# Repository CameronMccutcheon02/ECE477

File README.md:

# ECE477
Final Project Repository for ECE477 building an air hockey robot. 
Link to website repo: https://github.com/CameronMccutcheon02/ECE477Website

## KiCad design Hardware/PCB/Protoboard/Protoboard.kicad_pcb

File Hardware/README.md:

# ECE477
Hardware section of the ECE477 repository. This directory to contain all of the system diagrams, PCB files, etc relating to hardware of the robot

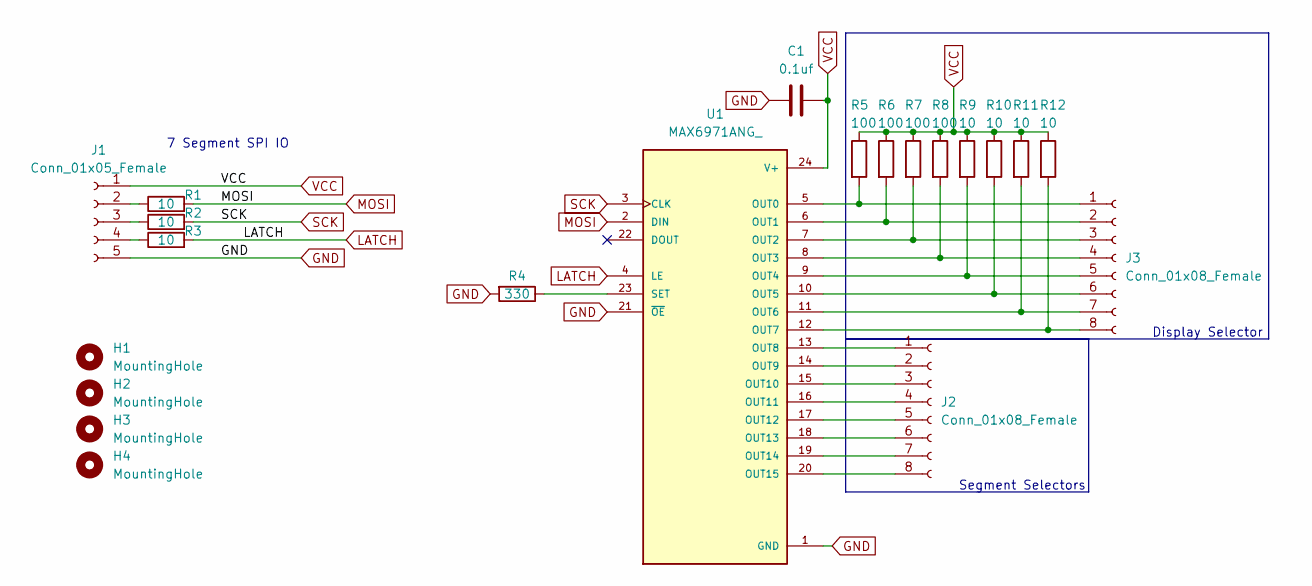
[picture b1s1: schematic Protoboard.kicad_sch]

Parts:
C1: 0.1uf; C_0805_2012Metric_Pad1.18x1.45mm_HandSolder
H1, H2, H3, H4: MountingHole; MountingHole_2.2mm_M2
J1: Conn_01x05_Female; PinSocket_1x05_P2.54mm_Vertical
J2, J3: Conn_01x08_Female; PinSocket_1x08_P2.54mm_Vertical
R1, R2, R3, R9, R10, R11, R12: 10; R_0805_2012Metric_Pad1.20x1.40mm_HandSolder
R4: 330; R_0805_2012Metric_Pad1.20x1.40mm_HandSolder
R5, R6, R7, R8: 100; R_0805_2012Metric_Pad1.20x1.40mm_HandSolder
U1: MAX6971ANG_; DIP794W47P254L3213H457Q24; PARTREV D

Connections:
GND: C1.1, J1.5, R4.2, U1.1 (GND), U1.21 (~OE)
LATCH: R3.2, U1.4 (LE)
MOSI: R1.2, U1.2 (DIN)
unnamed: J1.2, R1.1
unnamed: J1.3, R2.1
unnamed: J1.4, R3.1
unnamed: J2.1, U1.13 (OUT8)
unnamed: J2.2, U1.14 (OUT9)
unnamed: J2.3, U1.15 (OUT10)
unnamed: J2.4, U1.16 (OUT11)
unnamed: J2.5, U1.17 (OUT12)
unnamed: J2.6, U1.18 (OUT13)
unnamed: J2.7, U1.19 (OUT14)
unnamed: J2.8, U1.20 (OUT15)
unnamed: J3.1, R5.2, U1.5 (OUT0)
unnamed: J3.2, R6.2, U1.6 (OUT1)
unnamed: J3.3, R7.2, U1.7 (OUT2)
unnamed: J3.4, R8.2, U1.8 (OUT3)
unnamed: J3.5, R9.2, U1.9 (OUT4)
unnamed: J3.6, R10.2, U1.10 (OUT5)
unnamed: J3.7, R11.2, U1.11 (OUT6)
unnamed: J3.8, R12.2, U1.12 (OUT7)
unnamed: R4.1, U1.23 (SET)
SCK: R2.2, U1.3 (CLK)
VCC: C1.2, J1.1, R5.1, R6.1, R7.1, R8.1, R9.1, R10.1, R11.1, R12.1, U1.24 (V+)

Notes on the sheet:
Segment Selectors
7 Segment SPI IO
Display Selector

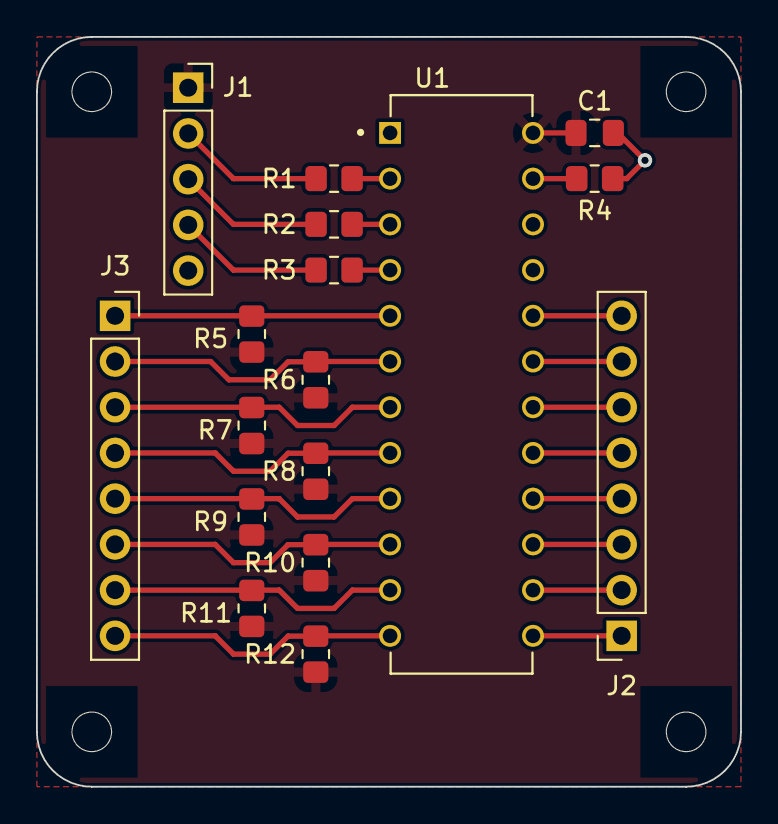
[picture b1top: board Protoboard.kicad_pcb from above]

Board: 2 copper layers, 39.1 x 41.7 mm, 21 parts (0 on the bottom side), 25 nets.

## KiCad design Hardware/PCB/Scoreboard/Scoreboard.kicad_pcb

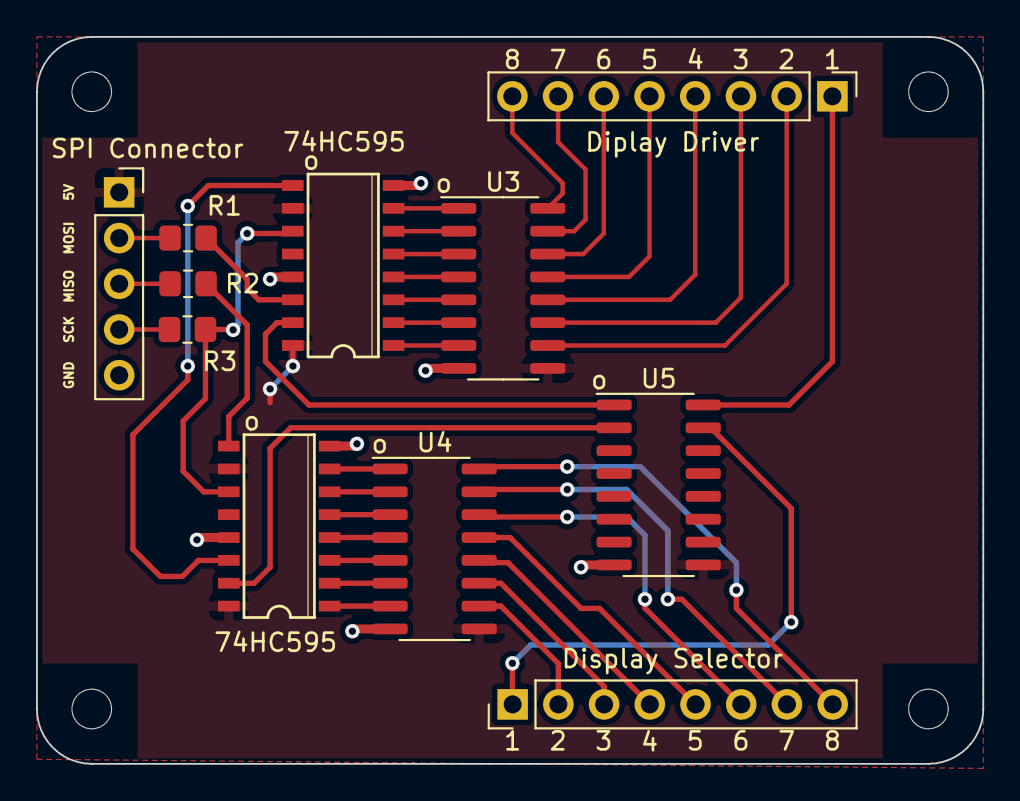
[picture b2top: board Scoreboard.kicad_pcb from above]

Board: 2 copper layers, 52.6 x 40.4 mm, 15 parts (0 on the bottom side), 41 nets.

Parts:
74HC595, 74HC595#2: 74HC595; SO16
Display Selector: Conn_01x08_Male; PinHeader_1x08_P2.54mm_Vertical
H1, H2, H3, H4: MountingHole; MountingHole_2.2mm_M2
J2: Conn_01x08_Male; PinHeader_1x08_P2.54mm_Vertical
R1, R2, R3: 10; R_0805_2012Metric_Pad1.20x1.40mm_HandSolder
SPI Connector: Conn_01x05_Female; PinSocket_1x05_P2.54mm_Vertical
U3, U4, U5: MC1413D; SOIC-16_3.9x9.9mm_P1.27mm

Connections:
/QA1: 74HC595.15 (QA), U5.1 (I1)
/QA2: 74HC595#2.15 (QA), U5.2 (I2)
/QB1: 74HC595.1 (QB), U3.7 (I7)
/QB2: 74HC595#2.1 (QB), U4.7 (I7)
/QC1: 74HC595.2 (QC), U3.6 (I6)
/QC2: 74HC595#2.2 (QC), U4.6 (I6)
/QD1: 74HC595.3 (QD), U3.5 (I5)
/QD2: 74HC595#2.3 (QD), U4.5 (I5)
/QE1: 74HC595.4 (QE), U3.4 (I4)
/QE2: 74HC595#2.4 (QE), U4.4 (I4)
/QF1: 74HC595.5 (QF), U3.3 (I3)
/QF2: 74HC595#2.5 (QF), U4.3 (I3)
/QG1: 74HC595.6 (QG), U3.2 (I2)
/QG2: 74HC595#2.6 (QG), U4.2 (I2)
/QH1: 74HC595.7 (QH), U3.1 (I1)
/QH2: 74HC595#2.7 (QH), U4.1 (I1)
/SPI1_MISO: 74HC595#2.9 (QH'), R2.2
/SPI1_MOSI: 74HC595.14 (SER), R1.2
/SPI1_SCK: 74HC595.11 (SRCLK), 74HC595#2.11 (SRCLK), R3.2
GND: 74HC595.8 (GND), 74HC595.13 (~OE), 74HC595#2.8 (GND), 74HC595#2.13 (~OE), SPI Connector.5, U3.8 (GND), U4.8 (GND), U5.8 (GND)
unnamed: R1.1, SPI Connector.2
unnamed: R2.1, SPI Connector.3
unnamed: R3.1, SPI Connector.4
unnamed: 74HC595.9 (QH'), 74HC595#2.14 (SER)
unnamed: J2.2, U3.10 (O7)
unnamed: J2.3, U3.11 (O6)
unnamed: J2.4, U3.12 (O5)
unnamed: J2.5, U3.13 (O4)
unnamed: J2.6, U3.14 (O3)
unnamed: J2.7, U3.15 (O2)
unnamed: J2.8, U3.16 (O1)
unnamed: Display Selector.2, U4.10 (O7)
unnamed: Display Selector.3, U4.11 (O6)
unnamed: Display Selector.4, U4.12 (O5)
unnamed: Display Selector.5, U4.13 (O4)
unnamed: Display Selector.6, U4.14 (O3)
unnamed: Display Selector.7, U4.15 (O2)
unnamed: Display Selector.8, U4.16 (O1)
unnamed: Display Selector.1, U5.15 (O2)
unnamed: J2.1, U5.16 (O1)
VCC: 74HC595.10 (~SRCLR), 74HC595.16 (VCC), 74HC595#2.10 (~SRCLR), 74HC595#2.16 (VCC), SPI Connector.1, U3.9 (COM), U4.9 (COM), U5.9 (COM)

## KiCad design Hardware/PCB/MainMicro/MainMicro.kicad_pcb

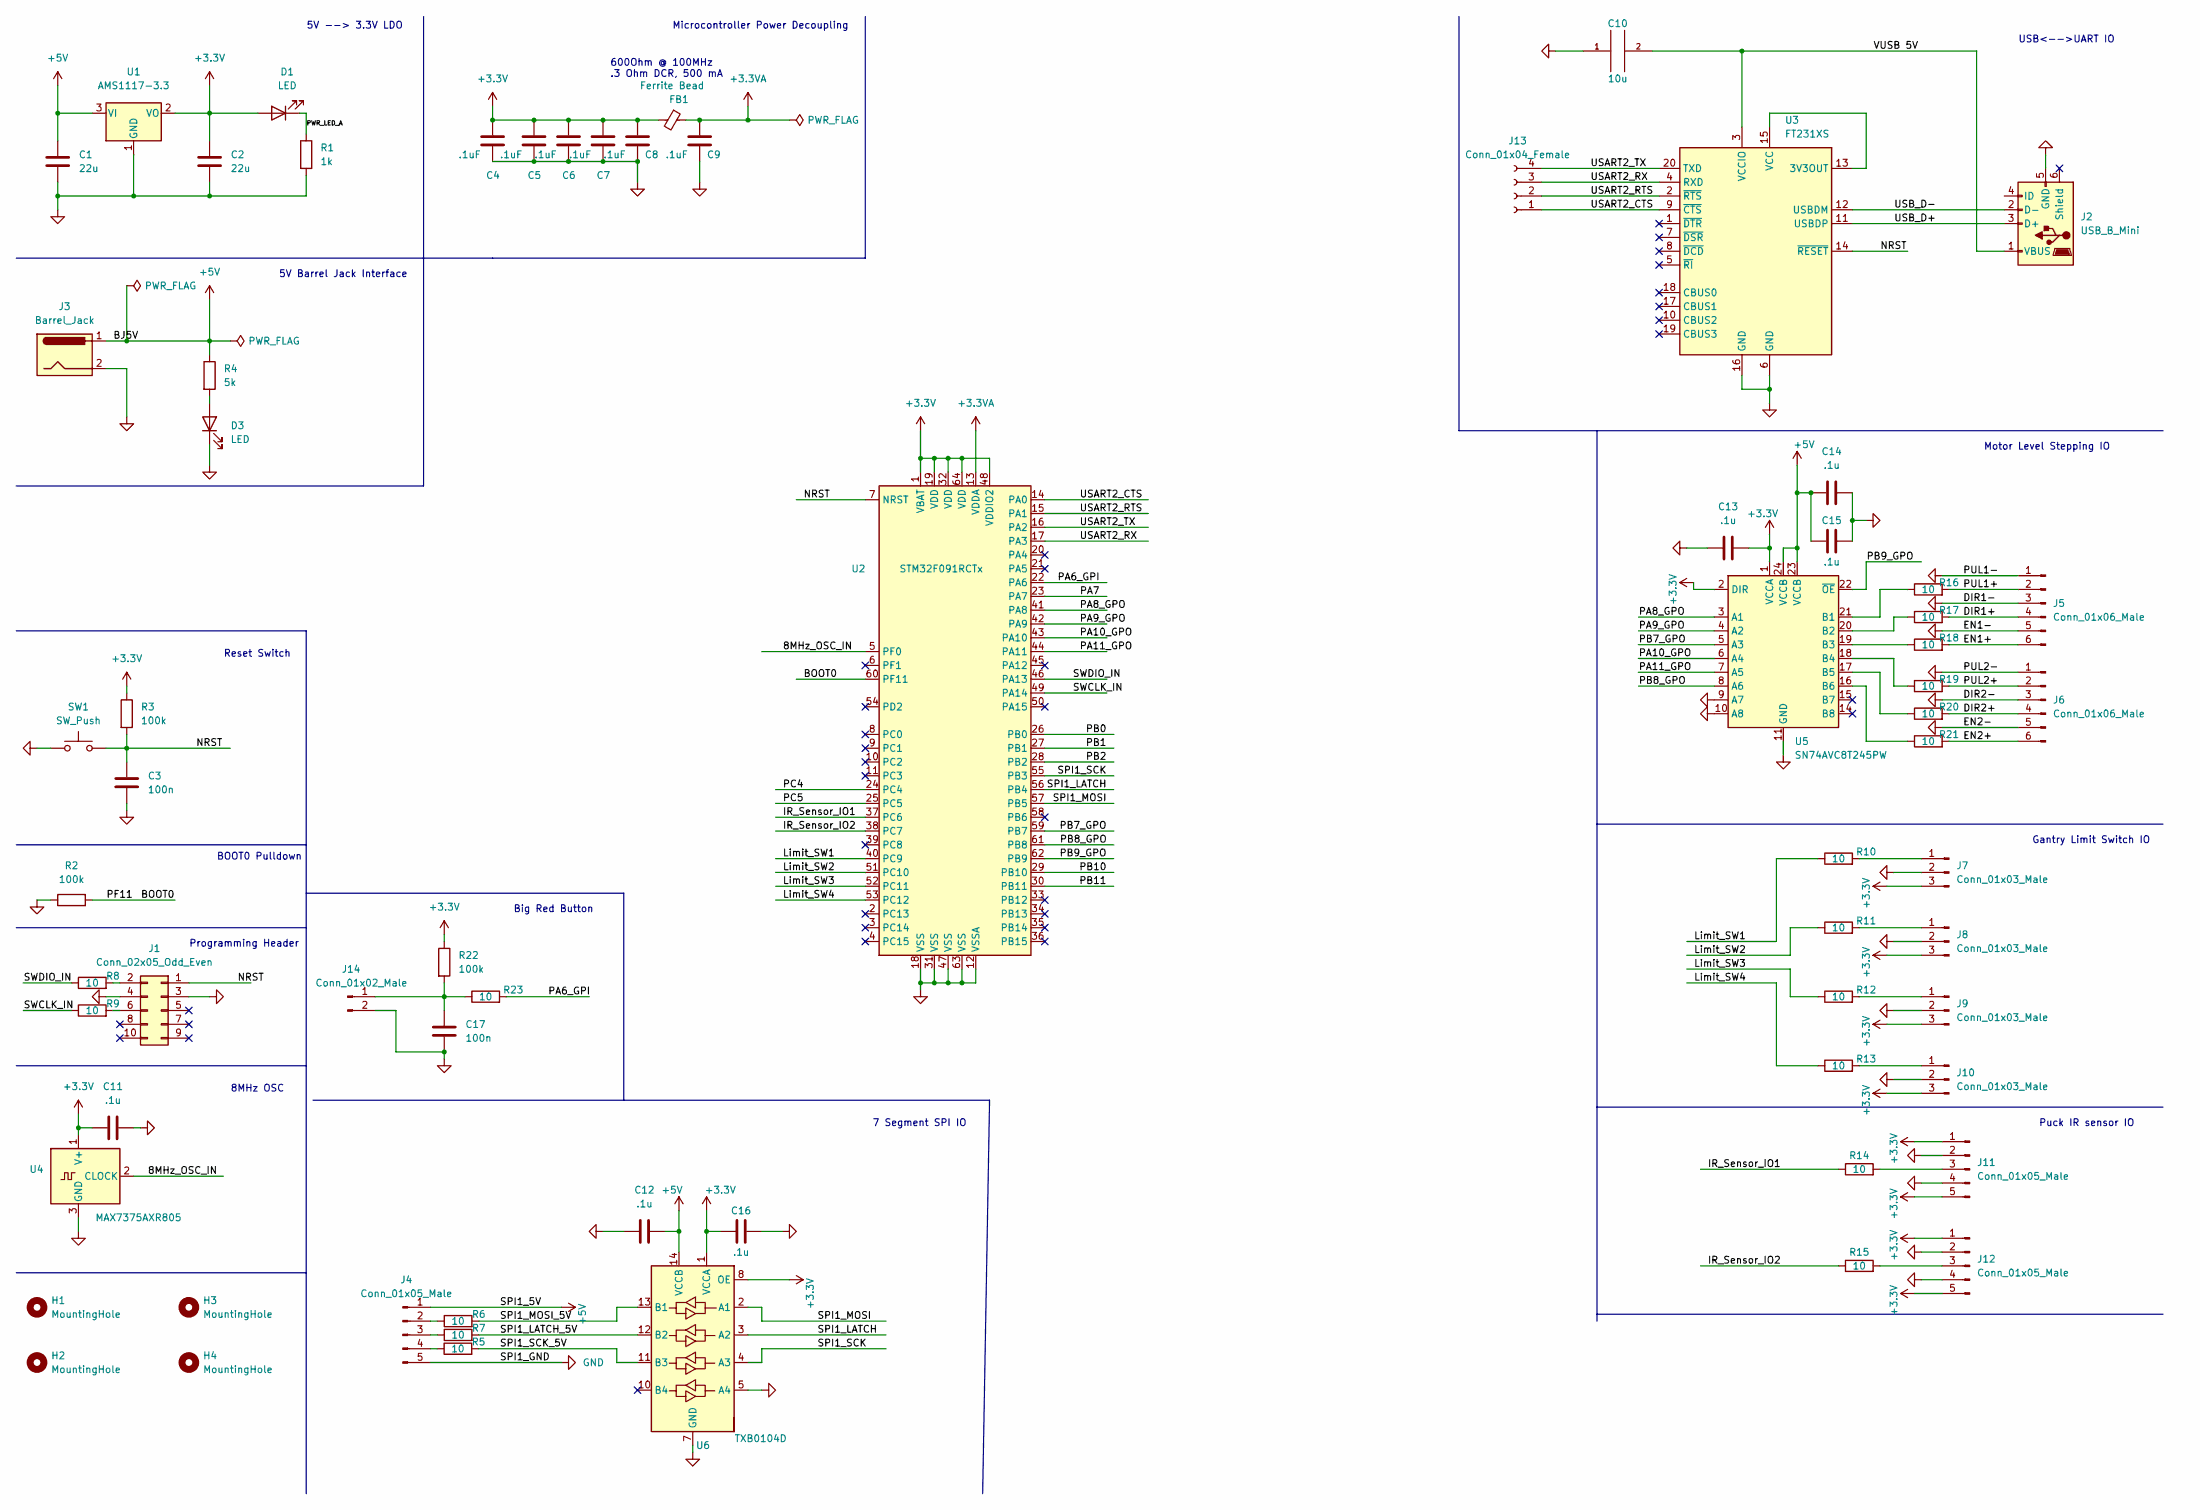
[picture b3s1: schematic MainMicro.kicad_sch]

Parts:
C1, C2: 22u; C_0805_2012Metric_Pad1.18x1.45mm_HandSolder
C3, C17: 100n; C_0805_2012Metric_Pad1.18x1.45mm_HandSolder
C4, C5, C6, C7, C8, C9: .1uF; C_0805_2012Metric_Pad1.18x1.45mm_HandSolder
C10: 10u; C_0805_2012Metric_Pad1.18x1.45mm_HandSolder
C11, C12, C13, C14, C15, C16: .1u; C_0805_2012Metric_Pad1.18x1.45mm_HandSolder
D1: LED; LED_0603_1608Metric_Pad1.05x0.95mm_HandSolder
D3: LED; LED_0805_2012Metric_Pad1.15x1.40mm_HandSolder
FB1: Ferrite Bead; L_0805_2012Metric_Pad1.15x1.40mm_HandSolder
H1, H2, H3, H4: MountingHole; MountingHole_2.7mm_M2.5
J1: Conn_02x05_Odd_Even; IDC-Header_2x05_P2.54mm_Latch_Vertical
J2: USB_B_Mini; USB_Micro-B_Amphenol_10118194_Horizontal
J3: Barrel_Jack; BarrelJack_CUI_PJ-102AH_Horizontal
J4, J11, J12: Conn_01x05_Male; JST_EH_B5B-EH-A_1x05_P2.50mm_Vertical
J5, J6: Conn_01x06_Male; JST_EH_B6B-EH-A_1x06_P2.50mm_Vertical
J7, J8, J9, J10: Conn_01x03_Male; JST_EH_B3B-EH-A_1x03_P2.50mm_Vertical
J13: Conn_01x04_Female; JST_EH_B4B-EH-A_1x04_P2.50mm_Vertical
J14: Conn_01x02_Male; JST_EH_B2B-EH-A_1x02_P2.50mm_Vertical
R1: 1k; R_0805_2012Metric_Pad1.20x1.40mm_HandSolder
R2, R3, R22: 100k; R_0805_2012Metric_Pad1.20x1.40mm_HandSolder
R4: 5k; R_0805_2012Metric_Pad1.20x1.40mm_HandSolder
R5, R6, R7, R8, R9, R10, R11, R12, R13, R14, R15, R16, R17, R18, R19, R20, R21, R23: 10; R_0805_2012Metric_Pad1.20x1.40mm_HandSolder
SW1: SW_Push; SW_SPST_PTS645
U1: AMS1117-3.3; SOT-223-3_TabPin2
U2: STM32F091RCTx; LQFP-64_10x10mm_P0.5mm
U3: FT231XS; SSOP-20_3.9x8.7mm_P0.635mm
U4: MAX7375AXR805; SOT-323_SC-70
U5: SN74AVC8T245PW; TSSOP-24_4.4x7.8mm_P0.65mm
U6: TXB0104D; SOIC-14_3.9x8.7mm_P1.27mm

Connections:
+3.3VA: C9.1, FB1.1, U2.13 (VDDA)
+3V3: C2.1, C4.1, C5.1, C6.1, C7.1, C8.1, C11.1, C13.1, C16.2, D1.2 (A), FB1.2, J7.3, J8.3, J9.3, J10.3, J11.1, J11.5, J12.1, J12.5, R3.1, R22.1, U1.2 (VO), U2.1 (VBAT), U2.19 (VDD), U2.32 (VDD), U2.48 (VDDIO2), U2.64 (VDD), U4.1 (V+), U5.1 (VCCA), U5.2 (DIR), U6.1 (VCCA), U6.8 (OE)
+5V: C1.1, C12.1, C14.2, C15.2, J3.1, J4.1, R4.1, U1.3 (VI), U5.23 (VCCB), U5.24 (VCCB), U6.14 (VCCB)
/8MHz_OSC_IN: U2.5 (PF0), U4.2 (CLOCK)
/BOOT0: R2.2, U2.60 (PF11)
/DIR1+: J5.4, R17.2
/DIR2+: J6.4, R20.2
/EN1+: J5.6, R18.2
/EN2+: J6.6, R21.2
/IR_Sensor_IO1: R14.1, U2.37 (PC6)
/IR_Sensor_IO2: R15.1, U2.38 (PC7)
/Limit_SW1: R10.1, U2.40 (PC9)
/Limit_SW2: R11.1, U2.51 (PC10)
/Limit_SW3: R12.1, U2.52 (PC11)
/Limit_SW4: R13.1, U2.53 (PC12)
/NRST: C3.1, J1.1, R3.2, SW1.2, U2.7 (NRST), U3.14 (~RESET)
/PA6_GPI: R23.2, U2.22 (PA6)
/PA7: U2.23 (PA7)
/PA8_GPO: U2.41 (PA8), U5.3 (A1)
/PA9_GPO: U2.42 (PA9), U5.4 (A2)
/PA10_GPO: U2.43 (PA10), U5.6 (A4)
/PA11_GPO: U2.44 (PA11), U5.7 (A5)
/PB0: U2.26 (PB0)
/PB1: U2.27 (PB1)
/PB2: U2.28 (PB2)
/PB7_GPO: U2.59 (PB7), U5.5 (A3)
/PB8_GPO: U2.61 (PB8), U5.8 (A6)
/PB9_GPO: U2.62 (PB9), U5.22 (~OE)
/PB10: U2.29 (PB10)
/PB11: U2.30 (PB11)
/PC4: U2.24 (PC4)
/PC5: U2.25 (PC5)
/PUL1+: J5.2, R16.2
/PUL2+: J6.2, R19.2
/PWR_LED_A: D1.1 (K), R1.1
/SPI1_LATCH: U2.56 (PB4), U6.3 (A2)
/SPI1_LATCH_5V: R7.2, U6.12 (B2)
/SPI1_MOSI: U2.57 (PB5), U6.2 (A1)
/SPI1_MOSI_5V: R6.2, U6.13 (B1)
/SPI1_SCK: U2.55 (PB3), U6.4 (A3)
/SPI1_SCK_5V: R5.2, U6.11 (B3)
/SWCLK_IN: R9.1, U2.49 (PA14)
/SWDIO_IN: R8.1, U2.46 (PA13)
/USART2_CTS: J13.1, U2.14 (PA0), U3.9 (~CTS)
/USART2_RTS: J13.2, U2.15 (PA1), U3.2 (~RTS)
/USART2_RX: J13.3, U2.17 (PA3), U3.4 (RXD)
/USART2_TX: J13.4, U2.16 (PA2), U3.20 (TXD)
/USB_D+: J2.3 (D+), U3.11 (USBDP)
/USB_D-: J2.2 (D-), U3.12 (USBDM)
/VUSB 5V: C10.2, J2.1 (VBUS), U3.3 (VCCIO)
GND: C1.2, C2.2, C3.2, C4.2, C5.2, C6.2, C7.2, C8.2, C9.2, C10.1, C11.2, C12.2, C13.2, C14.1, C15.1, C16.1, C17.2, D3.1 (K), J1.3, J1.4, J2.5 (GND), J3.2, J4.5, J5.1, J5.3, J5.5, J6.1, J6.3, J6.5, J7.2, J8.2, J9.2, J10.2, J11.2, J11.4, J12.2, J12.4, J14.2, R1.2, R2.1, SW1.1, U1.1 (GND), U2.12 (VSSA), U2.18 (VSS), U2.31 (VSS), U2.47 (VSS), U2.63 (VSS), U3.6 (GND), U3.16 (GND), U4.3 (GND), U5.9 (A7), U5.10 (A8), U5.11 (GND), U5.12 (GND), U5.13 (GND), U6.5 (A4), U6.7 (GND)
unnamed: C17.1, J14.1, R22.2, R23.1
unnamed: D3.2 (A), R4.2
unnamed: J1.2, R8.2
unnamed: J1.6, R9.2
unnamed: J4.2, R6.1
unnamed: J4.3, R7.1
unnamed: J4.4, R5.1
unnamed: J7.1, R10.2
unnamed: J8.1, R11.2
unnamed: J9.1, R12.2
unnamed: J10.1, R13.2
unnamed: J11.3, R14.2
unnamed: J12.3, R15.2
unnamed: R16.1, U5.21 (B1)
unnamed: R17.1, U5.20 (B2)
unnamed: R18.1, U5.19 (B3)
unnamed: R19.1, U5.18 (B4)
unnamed: R20.1, U5.17 (B5)
unnamed: R21.1, U5.16 (B6)
unnamed: U3.13 (3V3OUT), U3.15 (VCC)

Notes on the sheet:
USB<-->UART IO
Reset Switch
7 Segment SPI IO
8MHz OSC
Puck IR sensor IO
5V Barrel Jack Interface
Motor Level Stepping IO
BOOT0 Pulldown
5V --> 3.3V LDO
600Ohm @ 100MHz .3 Ohm DCR, 500 mA
Gantry Limit Switch IO
Microcontroller Power Decoupling
Programming Header
Big Red Button

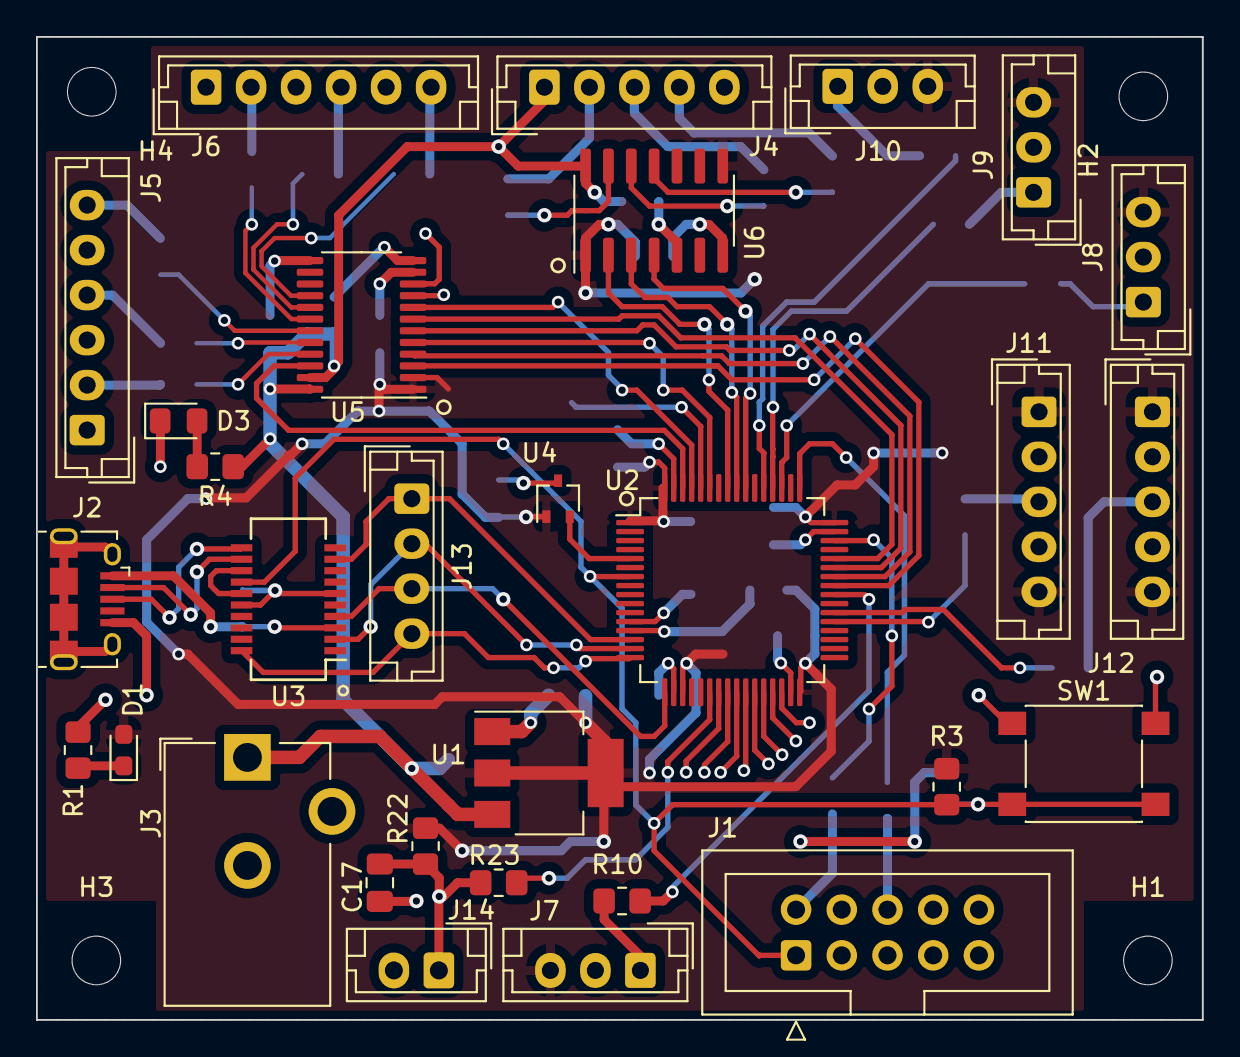
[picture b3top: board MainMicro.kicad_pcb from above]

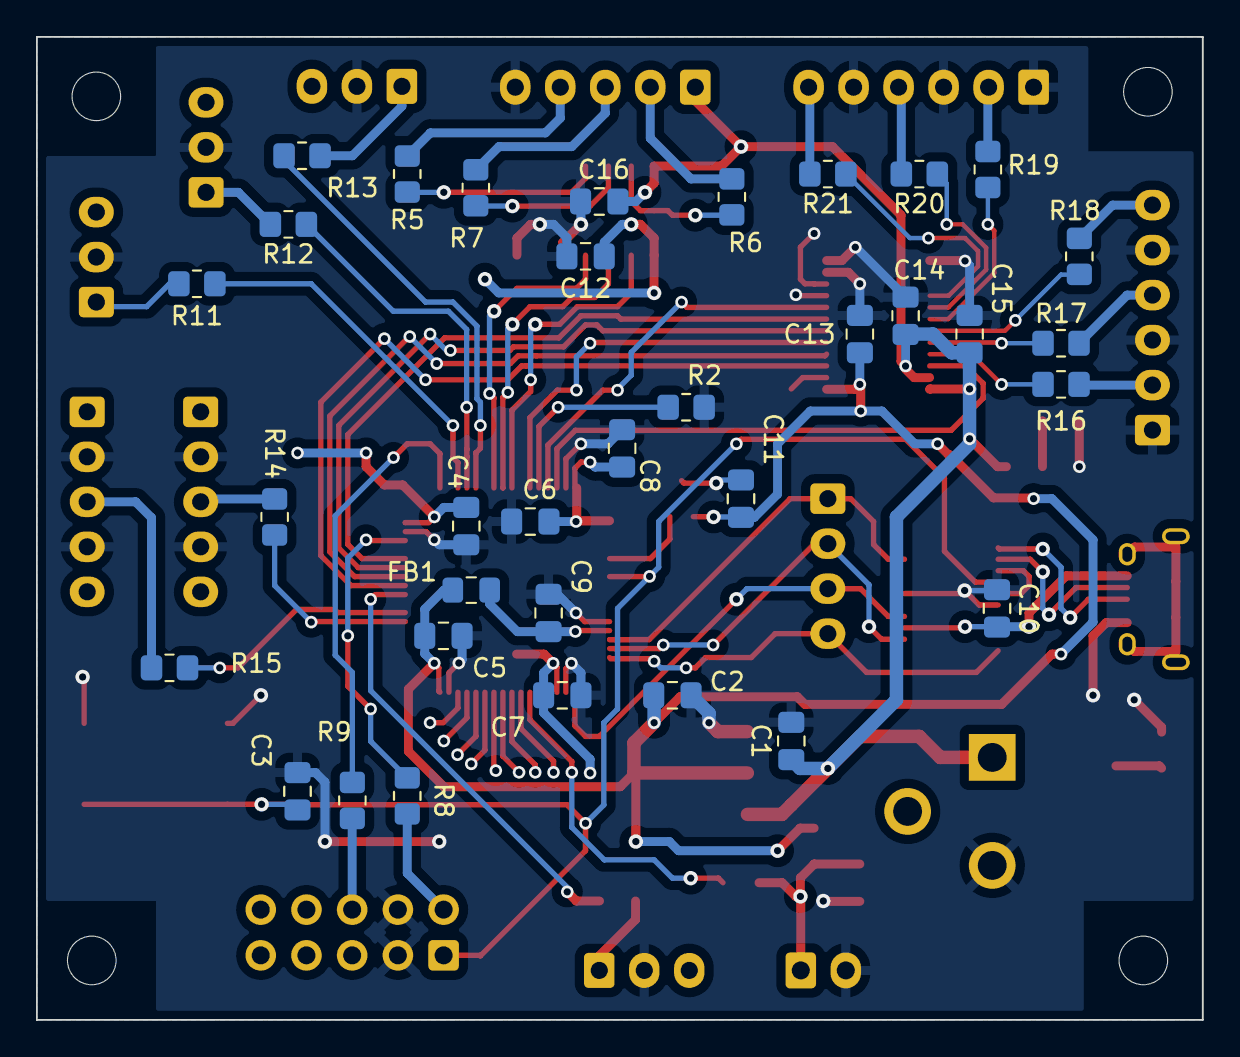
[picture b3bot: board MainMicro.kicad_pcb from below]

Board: 2 copper layers, 64.8 x 54.6 mm, 68 parts (34 on the bottom side), 63 nets.

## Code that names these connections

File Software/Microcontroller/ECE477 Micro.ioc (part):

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Mcu.Name=STM32F091R(B-C)Tx
Mcu.Package=LQFP64
Mcu.UserName=STM32F091RCTx
PA0.Mode=CTS_RTS
PA0.Signal=USART2_CTS
PA1.Mode=CTS_RTS
PA1.Signal=USART2_RTS
PA10.GPIOParameters=GPIO_Label
PA10.GPIO_Label=PUL_B
PA10.Signal=S_TIM1_CH3
PA11.GPIOParameters=GPIO_PuPd,GPIO_Label
PA11.GPIO_Label=DIR_B
PA11.GPIO_PuPd=GPIO_PULLDOWN
PA11.Signal=GPIO_Output
PA13.Mode=Serial_Wire
PA13.Signal=SYS_SWDIO
PA14.Mode=Serial_Wire
PA14.Signal=SYS_SWCLK
PA2.Mode=Asynchronous
PA2.Signal=USART2_TX
PA3.Mode=Asynchronous
PA3.Signal=USART2_RX
PA6.GPIOParameters=GPIO_Label
PA6.GPIO_Label=Test_Pin1
PA6.Signal=GPIO_Output
PA7.GPIOParameters=GPIO_Label
PA7.GPIO_Label=Test_Pin2
PA7.Signal=GPIO_Output
PA8.GPIOParameters=GPIO_Label
PA8.GPIO_Label=PUL_A
PA8.Signal=S_TIM1_CH1
PA9.GPIOParameters=GPIO_PuPd,GPIO_Label
PA9.GPIO_Label=DIR_A
PA9.GPIO_PuPd=GPIO_PULLDOWN
PA9.Signal=GPIO_Output
PB0.GPIOParameters=GPIO_Label
PB0.GPIO_Label=Test_Pin5
PB0.Signal=GPIO_Output
PB1.GPIOParameters=GPIO_Label
PB1.GPIO_Label=Test_Pin6
PB1.Signal=GPIO_Output
PB10.GPIOParameters=GPIO_Label
PB10.GPIO_Label=Test_Pin8
PB10.Signal=GPIO_Output
PB11.GPIOParameters=GPIO_Label
PB11.GPIO_Label=Test_Pin9
PB11.Signal=GPIO_Output
PB2.GPIOParameters=GPIO_Label
PB2.GPIO_Label=Test_Pin7
PB2.Signal=GPIO_Output
PB3.Mode=TX_Only_Simplex_Unidirect_Master
PB3.Signal=SPI1_SCK
PB4.Signal=SPI1_MISO
PB5.Mode=TX_Only_Simplex_Unidirect_Master
PB5.Signal=SPI1_MOSI
PB6.GPIOParameters=GPIO_PuPd,GPIO_Label
PB6.GPIO_Label=DIR_IC
PB6.GPIO_PuPd=GPIO_PULLDOWN
PB6.Signal=GPIO_Output
PB7.GPIOParameters=GPIO_PuPd,GPIO_Label
PB7.GPIO_Label=EN_A
PB7.GPIO_PuPd=GPIO_PULLUP
PB7.Signal=GPIO_Output
PB8.GPIOParameters=GPIO_PuPd,GPIO_Label
PB8.GPIO_Label=EN_B
PB8.GPIO_PuPd=GPIO_PULLUP
PB8.Signal=GPIO_Output
PB9.GPIOParameters=GPIO_PuPd,GPIO_Label
PB9.GPIO_Label=_OE
PB9.GPIO_PuPd=GPIO_PULLUP
PB9.Signal=GPIO_Output
PC10.GPIOParameters=GPIO_PuPd,GPIO_Label
PC10.GPIO_Label=Limit_SW2
PC10.GPIO_PuPd=GPIO_PULLDOWN
PC10.Signal=GPIO_Input
PC11.GPIOParameters=GPIO_PuPd,GPIO_Label
PC11.GPIO_Label=Limit_SW3
PC11.GPIO_PuPd=GPIO_PULLDOWN
PC11.Signal=GPIO_Input
PC12.GPIOParameters=GPIO_PuPd,GPIO_Label
PC12.GPIO_Label=Limit_SW4
PC12.GPIO_PuPd=GPIO_PULLDOWN
PC12.Signal=GPIO_Input
PC14OSC32_IN.Mode=LSE-External-Clock-Source
PC14OSC32_IN.Signal=RCC_OSC32_IN
PC4.GPIOParameters=GPIO_Label
PC4.GPIO_Label=Test_Pin3
PC4.Signal=GPIO_Output
PC5.GPIOParameters=GPIO_Label
PC5.GPIO_Label=Test_Pin4
PC5.Signal=GPIO_Output
PC6.GPIOParameters=GPIO_PuPd,GPIO_Label
PC6.GPIO_Label=IR_Sensor_IO1
PC6.GPIO_PuPd=GPIO_PULLDOWN
PC6.Signal=GPIO_Input
PC7.GPIOParameters=GPIO_PuPd,GPIO_Label
PC7.GPIO_Label=IR_Sensor_IO2
PC7.GPIO_PuPd=GPIO_PULLDOWN
PC7.Signal=GPIO_Input
PC9.GPIOParameters=GPIO_PuPd,GPIO_Label
PC9.GPIO_Label=Limit_SW1
PC9.GPIO_PuPd=GPIO_PULLDOWN
PC9.Signal=GPIO_Input
PF0-OSC_IN.Mode=HSE-External-Clock-Source
PF0-OSC_IN.Signal=RCC_OSC_IN
board=custom

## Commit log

2023-09-07 Setting up working directories
2023-09-07 Adds initial files
2023-09-07 Adds frame by frame prediction
2023-09-07 Starting PC/Micro Communications
2023-09-07 serial comms
2023-09-07 Added Purchase request excel sheet
2023-09-07 Fixed thing
2023-09-08 receiving data on stm
2023-09-08 Updated Notes
2023-09-08 Adds green puck request
2023-09-08 Updated Procurement Form
2023-09-10 initial commit for PCB design
2023-09-10 Initial setup for micro environment
2023-09-10 Fix small Mistake in RCC oscillator setup
2023-09-12 updating notes
2023-09-12 Started USB 2.0 Support Interface
2023-09-12 Small cleanup to sch
2023-09-12 added tracker
2023-09-12 serial comms update
2023-09-12 sending prediction to stm
2023-09-12 updated main.c
2023-09-13 comms progress
2023-09-14 notes
2023-09-14 Added Purchase Forms
2023-09-14 updated purchase form
2023-09-14 Adds predictive line to puck
2023-09-15 Adds predictions for bounce locations
2023-09-15 Removes unnecessary files
2023-09-16 More PCB stuff
2023-09-18 interfacing notes
2023-09-19 7-Seg interfacing
2023-09-19 Progress
2023-09-19 Puck Funnel Design
2023-09-19 PCB Power Supply + General Changes
2023-09-22 Adds future bounce predictions
2023-09-22 Adds threshold crossing detection
2023-09-28 Adds averaging functionality
2023-09-29 Uses averaging for point selection
2023-09-29 PCB workings
2023-10-02 Sensor Schematic
2023-10-03 updtes
2023-10-04 PCB footprint assignment
2023-10-04 PCB layout start
2023-10-05 Adds new video
2023-10-05 Actually adds new video
2023-10-05 update notes
2023-10-05 updated parsing test
2023-10-05 pyserial
2023-10-06 Adds compatibility for live feed
2023-10-08 Big PCB changes
2023-10-09 PCB passing DRC
2023-10-10 Shift Register Schematic and Motor Driver code.
2023-10-10 Fixed Joe concerns
2023-10-11 Added system diagram for John
2023-10-11 pain
2023-10-11 Small change
2023-10-11 Minor schematic changes and PCB dimensions
2023-10-12 Added Logic translation for SPI
2023-10-12 Updated PCBs
2023-10-13 updated serial comms
2023-10-13 cleaned folder
2023-10-13 updated stm file
2023-10-16 7 seg progress kinda
2023-10-17 Updating changes
2023-10-17 Added part links
2023-10-17 notes and procurement
2023-10-18 Basic Pin setup for code
2023-10-18 Main micro pinout
2023-10-18 adds displacement measurements
2023-10-18 adds green3.mp4
2023-10-18 added main micro workspace
2023-10-19 added 7segment code
2023-10-19 Updated notes for John
2023-10-19 modified stm code to look for direction from pc
2023-10-20 reworks stm code
2023-10-20 Please don't break
2023-10-20 Commit for PCB final
2023-10-20 Fixed LFS crashing
2023-10-20 Generated Main Micro Gerber Files
2023-10-20 Gerber FIle
2023-10-20 adds automatic color calibration
2023-10-20 Post joe
2023-10-21 Bunch of random backups that kicad did
2023-10-24 Protoboard Schematic with MAX6971 LED driver
2023-11-03 Protoboard layout.
2023-11-04 Backup change
2023-11-05 pcb assembly notes and cad
2023-11-06 updated pcb assembly notes
2023-11-06 Finished Protoboard
2023-11-06 Fixed Silkscreen
2023-11-06 Finished
2023-11-06 Dimensions
2023-11-09 Adds primitive distortion removal
2023-11-15 adds new calibration pics
2023-11-16 cleans up tracking code
2023-11-17 updated main
2023-11-17 adds static location movement
2023-11-17 cleans directory
2023-11-18 adds waiting functionality and software limit switches
2023-11-19 added notes and software stuff
2023-11-20 motor keys code
2023-11-20 updates track
2023-11-21 updated keys
2023-11-21 adds shadowing
2023-11-21 removes software limits
2023-11-28 Cam 7 seg
2023-11-29 added software backup code
2023-11-29 uploaded backup of working code
2023-11-29 one more copy of nice code
2023-11-30 main micro code backup
2023-12-01 pre-demo
2023-12-07 updated final code
2023-12-08 Spark Challenge Version
